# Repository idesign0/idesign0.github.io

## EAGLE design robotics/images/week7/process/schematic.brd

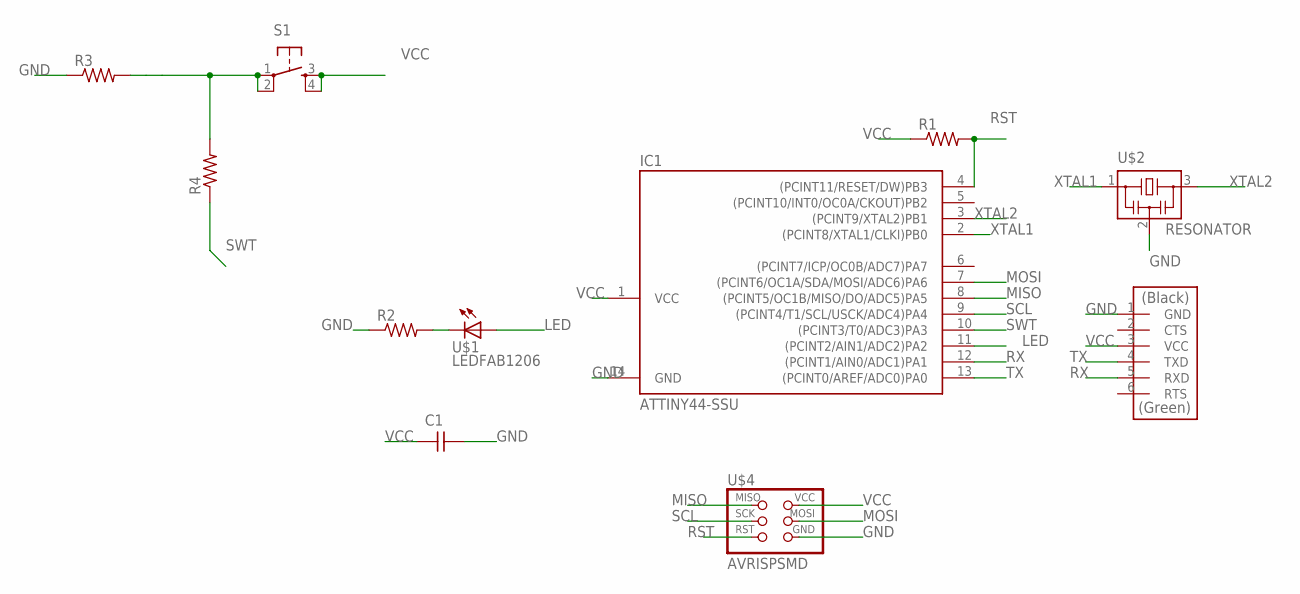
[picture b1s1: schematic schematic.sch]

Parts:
C1: CAP-UNPOLARIZEDFAB; C1206FAB
IC1: ATTINY44-SSU; SOIC14
R1, R2, R3, R4: RES-US1206FAB; R1206FAB
S1: 6MM_SWITCH6MM_SWITCH; 6MM_SWITCH
U$1: LEDFAB1206; LED1206FAB
U$2: RESONATOR; EFOBM
U$3: FTDI-SMD-HEADER; 1X06SMD
U$4: AVRISPSMD; 2X03SMD

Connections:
GND: C1.2, IC1.14 (GND), R2.1, R3.1, U$2.2, U$3.1 (GND), U$4.6 (GND)
LED: IC1.11 ((PCINT2/AIN1/ADC2)PA2), U$1.1 (A)
MISO: IC1.8 ((PCINT5/OC1B/MISO/DO/ADC5)PA5), U$4.1 (MISO)
MOSI: IC1.7 ((PCINT6/OC1A/SDA/MOSI/ADC6)PA6), U$4.4 (MOSI)
unnamed: R2.2, U$1.2 (C)
unnamed: R3.2, R4.2, S1.1, S1.2 (P1)
RST: IC1.4 ((PCINT11/RESET/DW)PB3), R1.2, U$4.5 (RST)
RX: IC1.12 ((PCINT1/AIN0/ADC1)PA1), U$3.5 (RXD)
SCL: IC1.9 ((PCINT4/T1/SCL/USCK/ADC4)PA4), U$4.3 (SCK)
SWT: IC1.10 ((PCINT3/T0/ADC3)PA3), R4.1
TX: IC1.13 ((PCINT0/AREF/ADC0)PA0), U$3.4 (TXD)
VCC: C1.1, IC1.1 (VCC), R1.1, S1.3 (S), S1.4 (S1), U$3.3 (VCC), U$4.2 (VCC)
XTAL1: IC1.2 ((PCINT8/XTAL1/CLKI)PB0), U$2.1
XTAL2: IC1.3 ((PCINT9/XTAL2)PB1), U$2.3

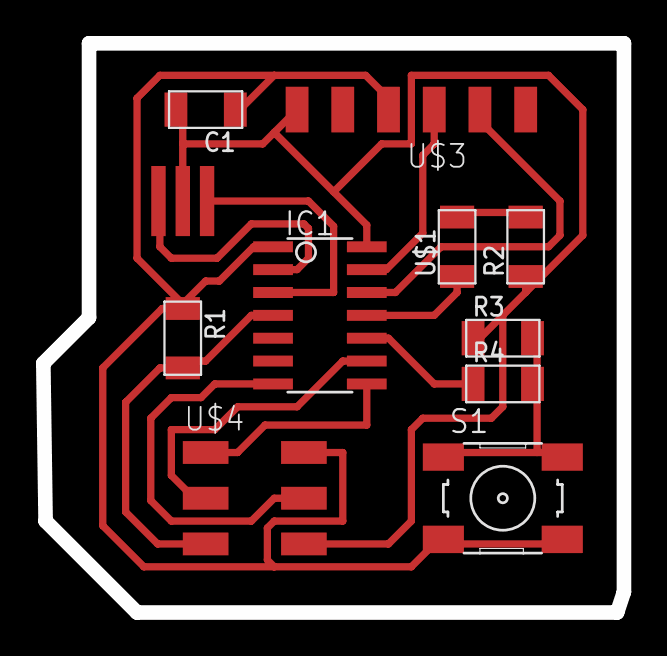
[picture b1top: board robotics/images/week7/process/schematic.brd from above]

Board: 2 copper layers, 32.3 x 31.6 mm, 11 parts (0 on the bottom side), 14 nets.

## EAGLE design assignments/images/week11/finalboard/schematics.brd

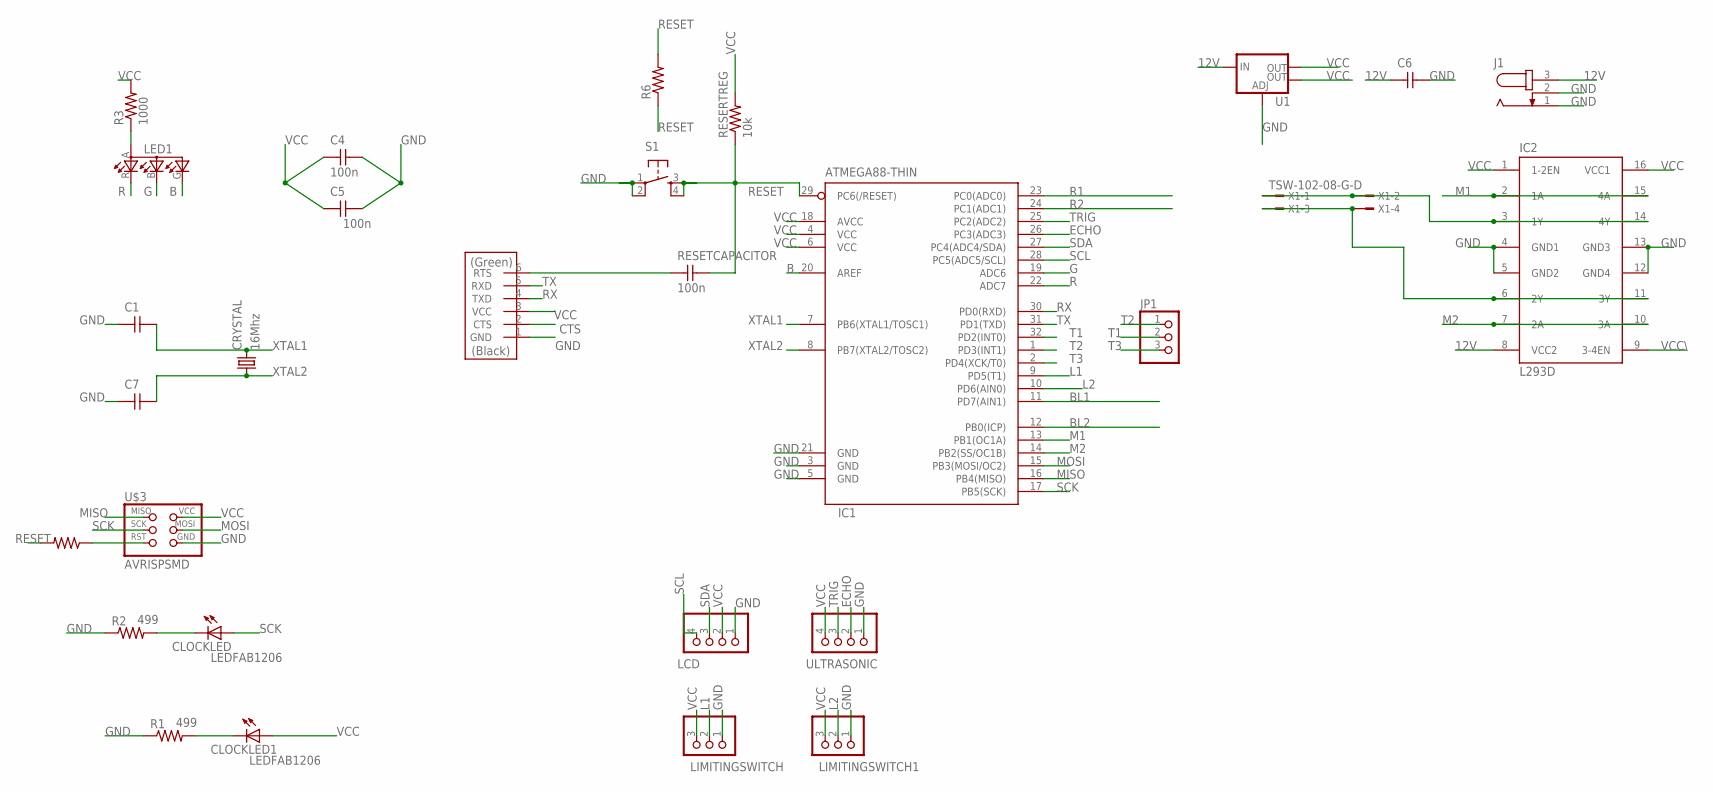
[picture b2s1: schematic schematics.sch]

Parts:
C1, C6, C7: CAP-UNPOLARIZEDFAB; C1206FAB
C4, C5: 100n; C1206FAB
CLOCKLED, CLOCKLED1: LEDFAB1206; LED1206FAB
CRYSTAL: 16Mhz; CSM-7X-DU
IC1: ATMEGA88-THIN; TQFP32-08THIN
IC2: L293D; DIL16
J1: JACK-PLUG1; SPC4078
JP1: PINHD-1X31X03_SMT; 1X03_SMT
LCD: PINHD-1X41X04_SMT; 1X04_SMT
LED1: LEDRGBOLD; P-LCC-4-3
LIMITINGSWITCH, LIMITINGSWITCH1: PINHD-1X31X03_SMT; 1X03_SMT
R1, R2: 499; R1206FAB
R3, R4, R6: 1000; R1206FAB
RESERTREG: 10k; R1206FAB
RESETCAPACITOR: 100n; C1206FAB
S1: 6MM_SWITCH6MM_SWITCH; 6MM_SWITCH
U1: V_REG_LM1117SOT223; SOT223
U$2: FTDI-SMD-HEADER; 1X06SMD
U$3: AVRISPSMD; 2X03SMD
ULTRASONIC: PINHD-1X41X04_SMT; 1X04_SMT
X1: TSW-102-08-G-D; TSW-102-XX-G-D

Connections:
12V: C6.1, IC2.8 (VCC2), J1.3, U1.3 (IN)
B: IC1.20 (AREF), LED1.G (CGREEN)
BL1: IC1.11 (PD7(AIN1))
BL2: IC1.12 (PB0(ICP))
CTS: U$2.2 (CTS)
ECHO: IC1.26 (PC3(ADC3)), ULTRASONIC.2
G: IC1.19 (ADC6), LED1.B (CBLUE)
GND: C1.1, C4.2, C5.2, C6.2, C7.1, IC1.3 (GND), IC1.5 (GND), IC1.21 (GND), IC2.4 (GND1), IC2.5 (GND2), IC2.12 (GND4), IC2.13 (GND3), J1.1, J1.2, LCD.1, LIMITINGSWITCH.1, LIMITINGSWITCH1.1, R1.1, R2.1, S1.1, S1.2 (P1), U1.1 (ADJ), U$2.1 (GND), U$3.6 (GND), ULTRASONIC.1
L1: IC1.9 (PD5(T1)), LIMITINGSWITCH.2
L2: IC1.10 (PD6(AIN0)), LIMITINGSWITCH1.2
M1: IC1.13 (PB1(OC1A)), IC2.2 (1A), IC2.15 (4A)
M2: IC1.14 (PB2(SS/OC1B)), IC2.7 (2A), IC2.10 (3A)
MISO: IC1.16 (PB4(MISO)), U$3.1 (MISO)
MOSI: IC1.15 (PB3(MOSI/OC2)), U$3.4 (MOSI)
unnamed: LED1.A (A2), R3.1
unnamed: CLOCKLED.2 (C), R2.2
unnamed: CLOCKLED1.2 (C), R1.2
unnamed: R4.1, U$3.5 (RST)
unnamed: RESETCAPACITOR.1, U$2.6 (RTS)
unnamed: IC2.3 (1Y), IC2.14 (4Y), X1.1, X1.2
unnamed: IC2.6 (2Y), IC2.11 (3Y), X1.3, X1.4
R: IC1.22 (ADC7), LED1.R (CRED)
R1: IC1.23 (PC0(ADC0))
R2: IC1.24 (PC1(ADC1))
RESET: IC1.29 (PC6(/RESET)), R4.2, R6.1, R6.2, RESERTREG.1, RESETCAPACITOR.2, S1.3 (S), S1.4 (S1)
RX: IC1.30 (PD0(RXD)), U$2.4 (TXD)
SCK: CLOCKLED.1 (A), IC1.17 (PB5(SCK)), U$3.3 (SCK)
SCL: IC1.28 (PC5(ADC5/SCL)), LCD.4
SDA: IC1.27 (PC4(ADC4/SDA)), LCD.3
T1: IC1.32 (PD2(INT0)), JP1.2
T2: IC1.1 (PD3(INT1)), JP1.1
T3: IC1.2 (PD4(XCK/T0)), JP1.3
TRIG: IC1.25 (PC2(ADC2)), ULTRASONIC.3
TX: IC1.31 (PD1(TXD)), U$2.5 (RXD)
VCC: C4.1, C5.1, CLOCKLED1.1 (A), IC1.4 (VCC), IC1.6 (VCC), IC1.18 (AVCC), IC2.1 (1-2EN), IC2.16 (VCC1), LCD.2, LIMITINGSWITCH.3, LIMITINGSWITCH1.3, R3.2, RESERTREG.2, U1.2 (OUT), U1.4 (OUT), U$2.3 (VCC), U$3.2 (VCC), ULTRASONIC.4
VCC\: IC2.9 (3-4EN)
XTAL1: C1.2, CRYSTAL.2, IC1.7 (PB6(XTAL1/TOSC1))
XTAL2: C7.2, CRYSTAL.1, IC1.8 (PB7(XTAL2/TOSC2))

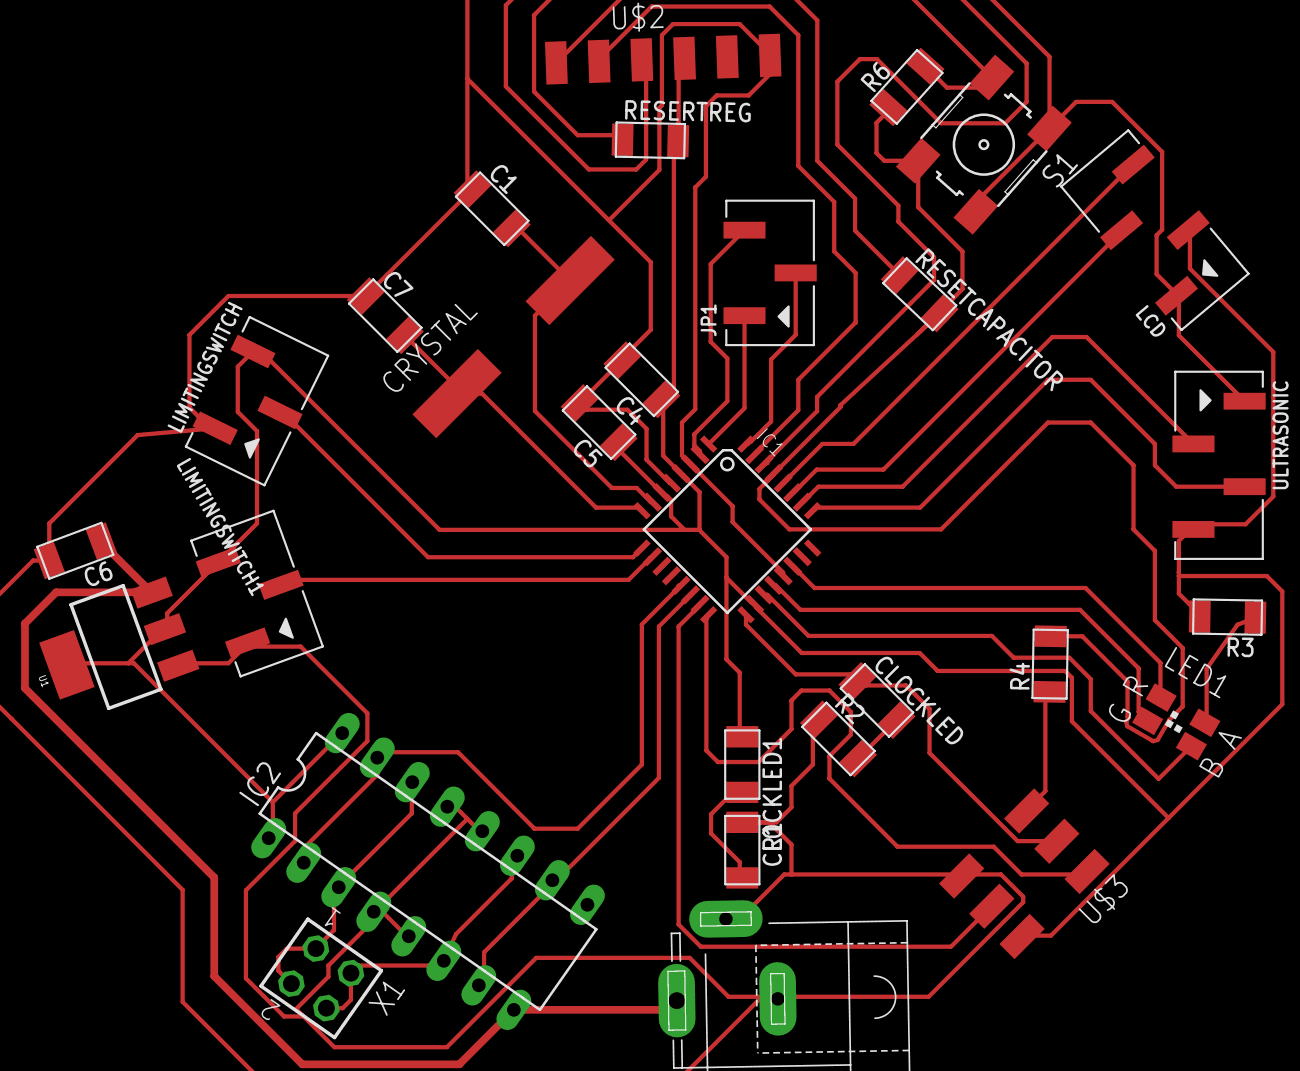
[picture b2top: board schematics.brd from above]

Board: 2 copper layers, 29 parts (0 on the bottom side), 32 nets.

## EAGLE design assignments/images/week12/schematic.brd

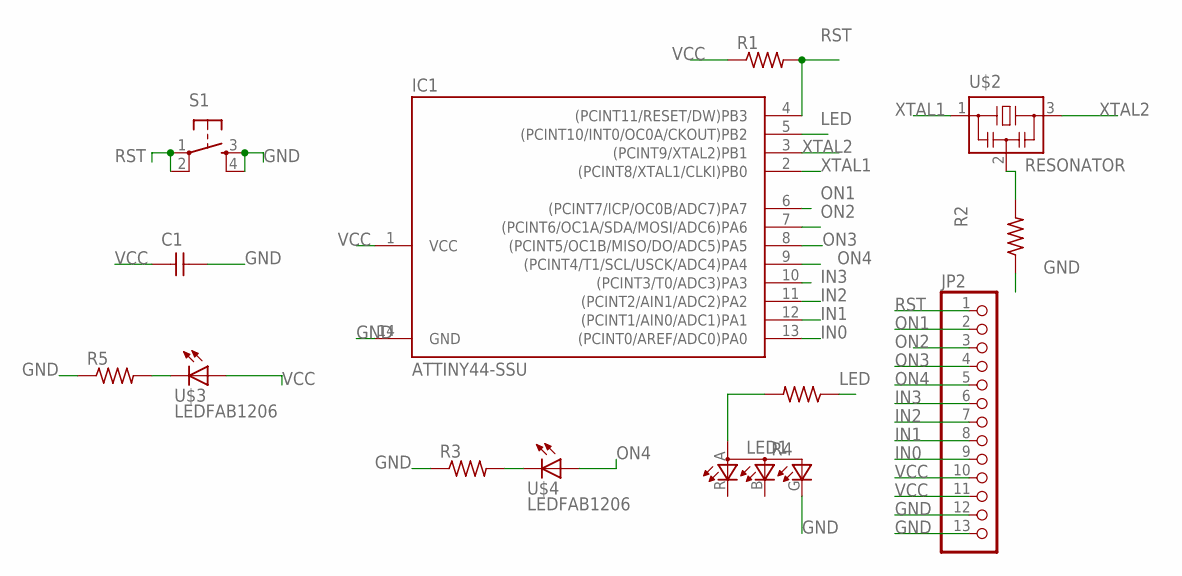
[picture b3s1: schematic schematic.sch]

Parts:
C1: CAP-UNPOLARIZEDFAB; C1206FAB
IC1: ATTINY44-SSU; SOIC14
JP2: PINHD-1X131X13_SMT; 1X13_SMT
LED1: LEDRGBOLD; P-LCC-4-3
R1, R2, R3, R4, R5: RES-US1206FAB; R1206FAB
S1: 6MM_SWITCH6MM_SWITCH; 6MM_SWITCH
U$2: RESONATOR; EFOBM
U$3, U$4: LEDFAB1206; LED1206FAB

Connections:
GND: C1.2, IC1.14 (GND), JP2.12, JP2.13, LED1.G (CGREEN), R2.1, R3.1, R5.1, S1.3 (S), S1.4 (S1)
IN0: IC1.13 ((PCINT0/AREF/ADC0)PA0), JP2.9
IN1: IC1.12 ((PCINT1/AIN0/ADC1)PA1), JP2.8
IN2: IC1.11 ((PCINT2/AIN1/ADC2)PA2), JP2.7
IN3: IC1.10 ((PCINT3/T0/ADC3)PA3), JP2.6
LED: IC1.5 ((PCINT10/INT0/OC0A/CKOUT)PB2), R4.1
unnamed: R2.2, U$2.2
unnamed: R5.2, U$3.2 (C)
unnamed: R3.2, U$4.2 (C)
unnamed: LED1.A (A2), R4.2
ON1: IC1.6 ((PCINT7/ICP/OC0B/ADC7)PA7), JP2.2
ON2: IC1.7 ((PCINT6/OC1A/SDA/MOSI/ADC6)PA6), JP2.3
ON3: IC1.8 ((PCINT5/OC1B/MISO/DO/ADC5)PA5), JP2.4
ON4: IC1.9 ((PCINT4/T1/SCL/USCK/ADC4)PA4), JP2.5, U$4.1 (A)
RST: IC1.4 ((PCINT11/RESET/DW)PB3), JP2.1, R1.2, S1.1, S1.2 (P1)
VCC: C1.1, IC1.1 (VCC), JP2.10, JP2.11, R1.1, U$3.1 (A)
XTAL1: IC1.2 ((PCINT8/XTAL1/CLKI)PB0), U$2.1
XTAL2: IC1.3 ((PCINT9/XTAL2)PB1), U$2.3

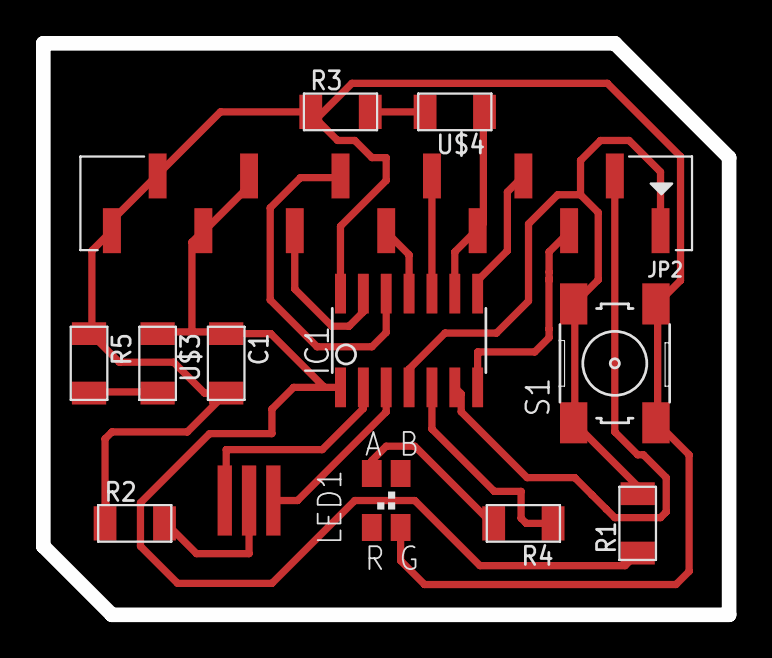
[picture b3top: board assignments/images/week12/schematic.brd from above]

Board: 2 copper layers, 38.1 x 31.8 mm, 13 parts (0 on the bottom side), 18 nets.

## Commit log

2019-07-03 starting new web page
2019-07-03 minor corrections
2019-07-05 added stype on future home page
    added required styling on future home page ! links are remained to give !
2019-07-06 modifications in index and blog
2019-07-06 mobile view modification
2019-07-06 updarted
2019-07-06 mods on logo
2019-07-06 checkpoint on blog page
2019-07-06 mods
2019-07-06 checkpoint
2019-07-06 majority changes done
2019-07-18 changes in contact
2019-07-18 htacsess
2019-11-13 starting about robotics
2019-12-27 added github linl
2020-06-04 front page updates
2020-06-10 updates in front page
2020-06-14 WEEK 1 Changes in to monitor
2020-06-16 week 2 modifications
2020-06-17 WEEK 2 Changes in to monitor
2020-06-17 WEEK 2 Changes in to mobile
2020-06-19 week 2
2020-06-25 changes in large screen
2020-06-30 test
2020-07-01 week 3
2020-07-01 styling changes in week 3
2020-07-02 changes in week 3
2020-07-02 Changes till inkscape
2020-07-02 changes in raster section !
2020-07-04 week 3 updated !
2020-08-17 idesign
2020-08-18 week 4 start
2020-08-19 week 4 complete to vinyl cutting
2020-08-21 week 4 complete to comb test
2020-08-21 week 4 complete
2020-08-25 week 5 starting
2020-08-26 week 5 start
2020-08-29 week 5 electronic components
2020-08-29 machine set to mdx 20
2020-08-29 till offset overlay
2020-08-30 week 5 complete
2020-08-31 starting week 6
2020-08-31 week 6 finish
2020-08-31 week 6 mobile update
2020-09-01 week 7 started
2020-09-01 week 7 finish
2020-09-01 week 7 footer
2020-09-05 week 8 start
2020-09-05 till "Redesign of Gear box in fusion360"
2020-09-05 week 8 complete
2020-09-07 week 9 started
2020-09-07 week 9 complete
2020-09-07 week 9 update
2020-09-08 week 10 start
2020-09-10 week 10
2020-09-10 MATERIAL SIZE AND MARGINS
2020-09-14 week 10 finished
2020-09-14 week 11 started
2020-09-15 week 11 finish
2020-09-16 week 12 complete
2020-09-17 week 13 finish
2020-09-19 week 17
2020-09-20 week 15
2020-09-20 week 14 started
2020-09-20 week 14 finish
2020-09-22 week 15 finish !
2020-09-23 finish till week 17
2020-09-23 week 18 finish
2020-09-23 week 19 finish
2020-09-23 week 19 and project finish
2020-09-23 till finger joints
2020-09-23 till CAD DESIGNS
2020-09-24 week 20 final project finish
2020-09-25 final project file
2020-09-25 about page complete
2020-09-25 update footer
2020-09-27 update on contact
2020-10-30 new project page
2020-10-30 remove html
2020-10-31 updates in prostheticshand
2020-11-01 till 3d printing
2020-11-01 3d printing
2020-11-02 update 3d printing
2020-11-03 till drawbacks
2020-11-04 drawbacks finish
2020-11-04 conclusions
2020-11-04 grammer corrections
2020-11-04 grammar corrections
2020-11-06 spring design mechanism
2020-11-07 cad full model
2020-11-07 update till full model video
2020-11-10 conclution
2020-11-10 grammar corrected
2020-11-11 update-highlights
2020-12-07 headphones
2020-12-07 symphony page
2020-12-08 BMW Z4
2020-12-15 nano e commuter
2021-09-04 added nweek 15(missing link)
2022-03-07 added robotics page
2023-06-15 Update in About - resume file and list
2023-06-15 about update
